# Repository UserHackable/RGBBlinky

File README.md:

## RGBBlinkyCR2032 

### Board dimensions

* (130000, 170000) original units
* (1.3000, 1.7000) inches
* (33.0200, 43.1800) mm

| Front | Back |
| --- | --- |
|  |  |

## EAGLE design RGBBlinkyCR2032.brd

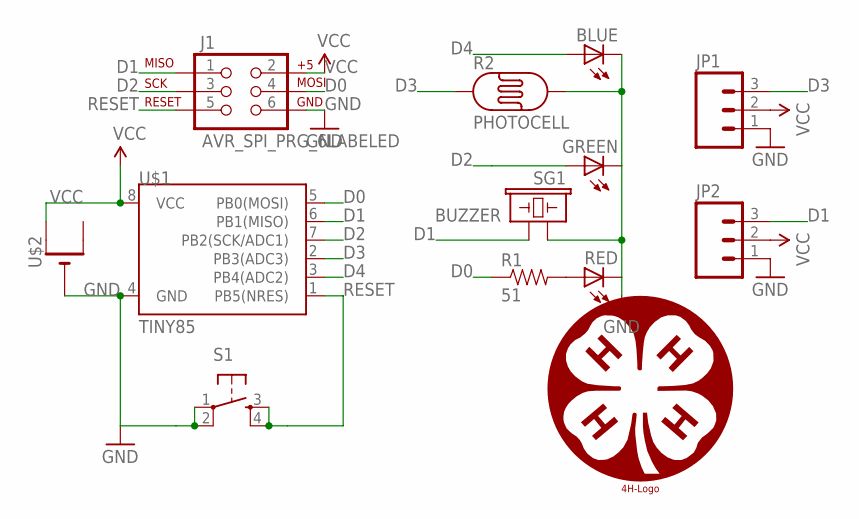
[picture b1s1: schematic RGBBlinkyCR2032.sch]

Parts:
BLUE: LED5MM
GREEN: LED5MM
J1: AVR_SPI_PRG_6LABELED; 2X3-NS
JP1, JP2: M03PTH; 1X03
R1: 51; AXIAL-0.3
R2: PHOTOCELL
RED: LED5MM
S1: TAC_SWITCHPTH; TACTILE-PTH
SG1: BUZZER; BUZZER-12MM
U$1: TINY85; DIP08
U$2: CR2032THM; CR2032-THRU
U$4: 4H-LOGO6; 4H_LOGO_6

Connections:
D0: J1.4 (MOSI), R1.P$1 (1), U$1.5 (PB0(MOSI))
D1: J1.1 (MISO), JP2.3, SG1.- (2), U$1.6 (PB1(MISO))
D2: GREEN.A, J1.3 (SCK), U$1.7 (PB2(SCK/ADC1))
D3: JP1.3, R2.1, U$1.2 (PB3(ADC3))
D4: BLUE.A, U$1.3 (PB4(ADC2))
GND: BLUE.K (C), GREEN.K (C), J1.6 (GND), JP1.1, JP2.1, R2.2, RED.K (C), S1.1, S1.2, SG1.+ (1), U$1.4 (GND), U$2.-
unnamed: R1.P$2 (2), RED.A
RESET: J1.5 (RST), S1.3, S1.4, U$1.1 (PB5(NRES))
VCC: J1.2 (V+), JP1.2, JP2.2, U$1.8 (VCC), U$2.+1 (+)

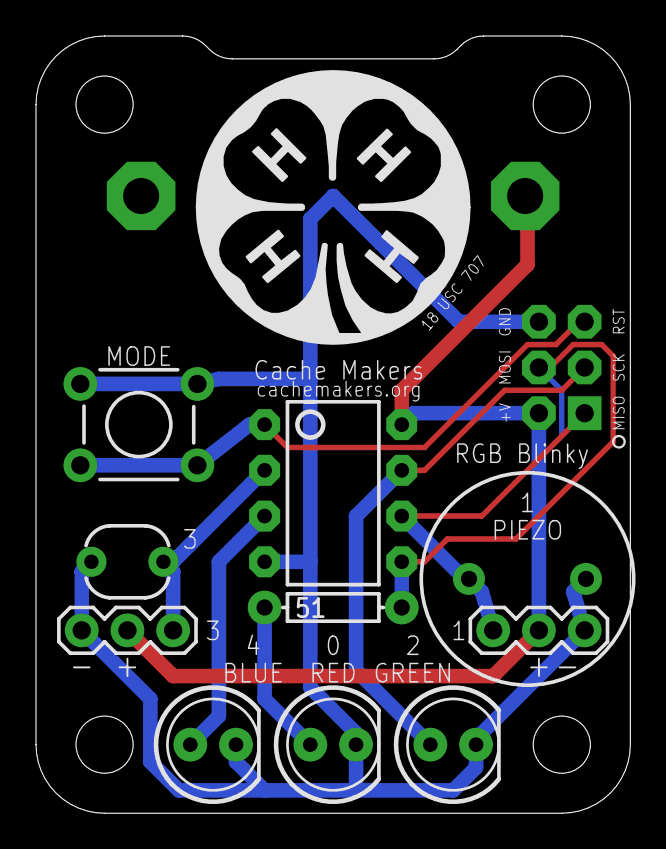
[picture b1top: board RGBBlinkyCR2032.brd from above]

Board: 2 copper layers, 33.0 x 43.2 mm, 13 parts (1 on the bottom side), 9 nets.

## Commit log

2016-04-07 updating battery
2016-04-07 4H foo
2016-04-07 updating logo
2016-04-07 upating files
2016-04-07 updating files
2016-04-07 from Makefile

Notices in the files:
parts and their libraries:
SparkFun-LED: Licensing: Creative Commons ShareAlike 4.0 International - https://creativecommons.org/licenses/by-sa/4.0
